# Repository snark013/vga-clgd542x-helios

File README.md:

# Helios VGA Card

[Русская версия](README_RU.md)

Main project repository: [git.snark13.com/snark13/helios](https://git.snark13.com/snark13/helios.git).

GitHub mirror: [github.com/snark013/vga-clgd542x-helios](https://github.com/snark013/vga-clgd542x-helios).

Helios is a VGA graphics card for the 16-bit ISA bus, based on Cirrus Logic CL-GD542x chips (CL-GD5422–CL-GD5429). The project is designed in KiCad and uses a two-layer PCB.

## Project status

The current schematic and PCB version is 1.2.7. The following configurations have been built and tested:

| PCB version | Graphics chip | Video memory |
| --- | --- | --- |
| 0.3 | CL-GD5422 | 512 KB |
| 1.2.5 | CL-GD5429 | 1 MB |

Other combinations of PCB revision, graphics chip, and memory capacity have not yet been tested.

Release files for version 1.2.7 are available in the repository. The test results above apply to versions 0.3 and 1.2.5.

## Key features

- VGA compatibility.
- Integrated video digital-to-analog converter (RAMDAC) with True Color support.
- Three video memory configurations: 512 KB, 1 MB, or 2 MB, depending on the graphics chip.
- Two-layer PCB for the 16-bit ISA bus.

## Video memory configurations

| Capacity | Chips to populate | Graphics chips |
| --- | --- | --- |
| 512 KB | U1 | CL-GD5422–CL-GD5424 |
| 1 MB | U1, U2 | CL-GD5422–CL-GD5429 |
| 2 MB | U1–U4 | CL-GD5426–CL-GD5429 |

This table lists the intended configurations. Configurations tested on hardware are listed under “Project status”.

## Project files

- [helios.kicad_pro](helios.kicad_pro) — KiCad project.
- [helios.kicad_sch](helios.kicad_sch) — schematic.
- [helios.kicad_pcb](helios.kicad_pcb) — PCB layout.
- [helios.pretty/](helios.pretty/) — local footprint library.
- [docs/](docs/) — reference documentation.
- [release/](release/) — release files and previous version files.
- [images/1.2.5/](images/1.2.5/) — photos of the assembled version 1.2.5 board.

### Release files

| Version | Gerber files | Schematic | Interactive bill of materials |
| --- | --- | --- | --- |
| 1.2.7 | [ZIP](release/1.2.7/helios-1.2.zip) | [PDF](release/1.2.7/helios.pdf) | [HTML](release/1.2.7/ibom.html) |
| 1.2.5 | [ZIP](release/1.2.5/helios.zip) | [PDF](release/1.2.5/helios.pdf) | [HTML](release/1.2.5/ibom.html) |

## Configuration and assembly

Component references below apply to the current revision unless stated otherwise. Check the configuration input settings against the [CL-GD542x Technical Reference Manual](docs/CL-GD542X_Technical_Reference_Manual_Jan1994.pdf) for the graphics chip being used.

### Configuration resistors

| Reference | Function |
| --- | --- |
| R9 | Zero-wait-state BIOS access (except CL-GD5429) |
| R10 | Sleep control port selection: 3C3h / 4E68h |
| R11, R12 | DRAM clock selection: 50 / 44 / 41 / 38 MHz |
| R13 | DRAM timing configuration |
| R14 | DRAM multi CAS/WE configuration |

By default, fit all resistors listed above except R10.

### Current reference

Fit only one of the two alternatives: **U5 or U5′**. These options use LM334 devices with different pinouts; select the appropriate package when assembling the board.

### Configuration jumpers

| Reference | Function |
| --- | --- |
| JP5 | Enable IRQ2 |
| JP6 | Zero-wait-state ISA operation |
| JP7 | BIOS ROM section selection |

JP6 is fitted by default.

Revisions earlier than 1.2.7 also include JP8 and JP9 to select the ROM read signal (MEMR / EROM / GND). On those boards, connect JP9 to ground. JP8 and JP9 have been removed starting with revision 1.2.7.

### Clock source

Two options are provided for the 14.318 MHz clock:

- ISA bus BOSC signal: fit R16.
- On-board oscillator: fit Y1, C17, and C18.

## BIOS preparation

A BIOS image from another graphics card may need conversion before it can be programmed into the Helios ROM.

Many original boards use a BIOS arranged for 16-bit operation with two ROM chips. The least significant address bit is used as the chip’s most significant address bit to switch between the two halves of its contents. This arrangement is described in the graphics chip documentation.

Helios uses linear (“flat”) addressing, so images with a different address arrangement must be converted. Some original boards already use linear addressing; their images do not require this conversion.

Revision **0.3** also has the BIOS data lines connected in reverse order: D0–D7 are wired as D7–D0. Images prepared for this revision must also have the bit order reversed within each byte.

## Revision history

### 1.2.7

- Corrected the mislabeled U8 device type from 74LS541 to 74LS245.
- Removed JP8 and JP9.
- Removed unnecessary PCB markings and corrected inaccurate ones.

### 1.2.5

- Optimized component placement.
- Changed all capacitors below 0.1 µF to the 0603 package.
- Added diode protection to the VGA output lines.
- Built the second working board version.

### 1.2.2

- Optimized component placement.
- Renumbered components.

### 0.7

- Added an alternative HC-49 footprint for the 14.318 MHz oscillator.

### 0.5

- Added support for an on-board 14.318 MHz oscillator (two-pin 5032 package).
- Added support for the LM334SM with an alternative pinout as a current reference.
- Corrected the BIOS data bus routing.
- Added termination resistors to the address bus lines between the graphics chip and memory.
- Renumbered components.

### 0.3

- Built the first working board, codenamed Lemon.
- Identified the reversed BIOS data line order (D0–D7 → D7–D0); the BIOS image requires a corresponding conversion.

## Photos

Assembled version 1.2.5 board.

[Photo of the revision 0.3 board](images/0.3/build-0.3.jpg).

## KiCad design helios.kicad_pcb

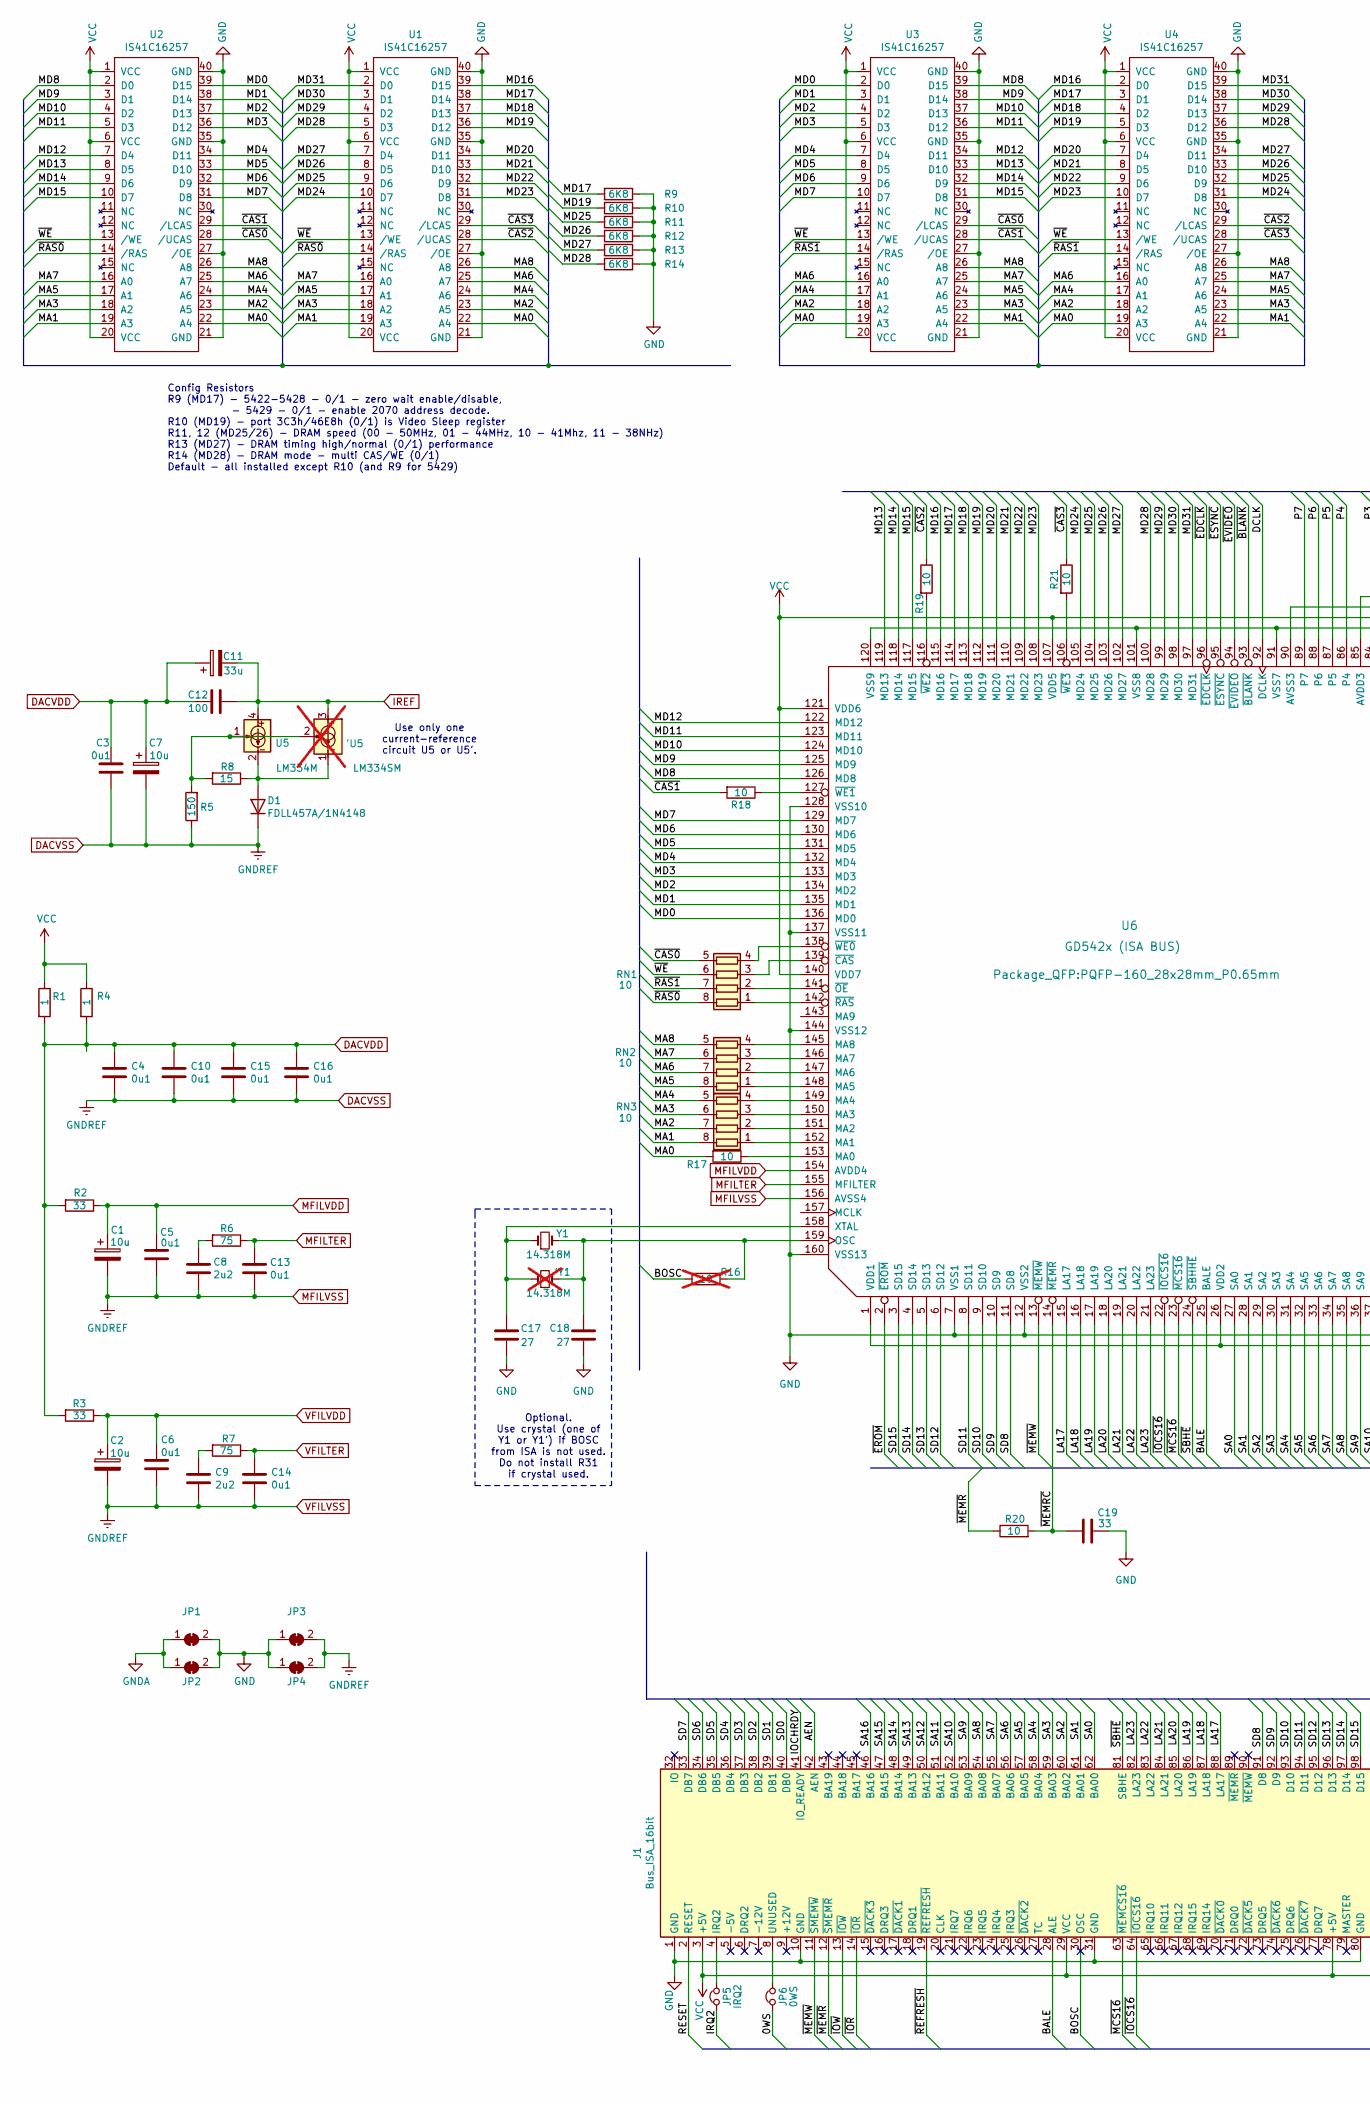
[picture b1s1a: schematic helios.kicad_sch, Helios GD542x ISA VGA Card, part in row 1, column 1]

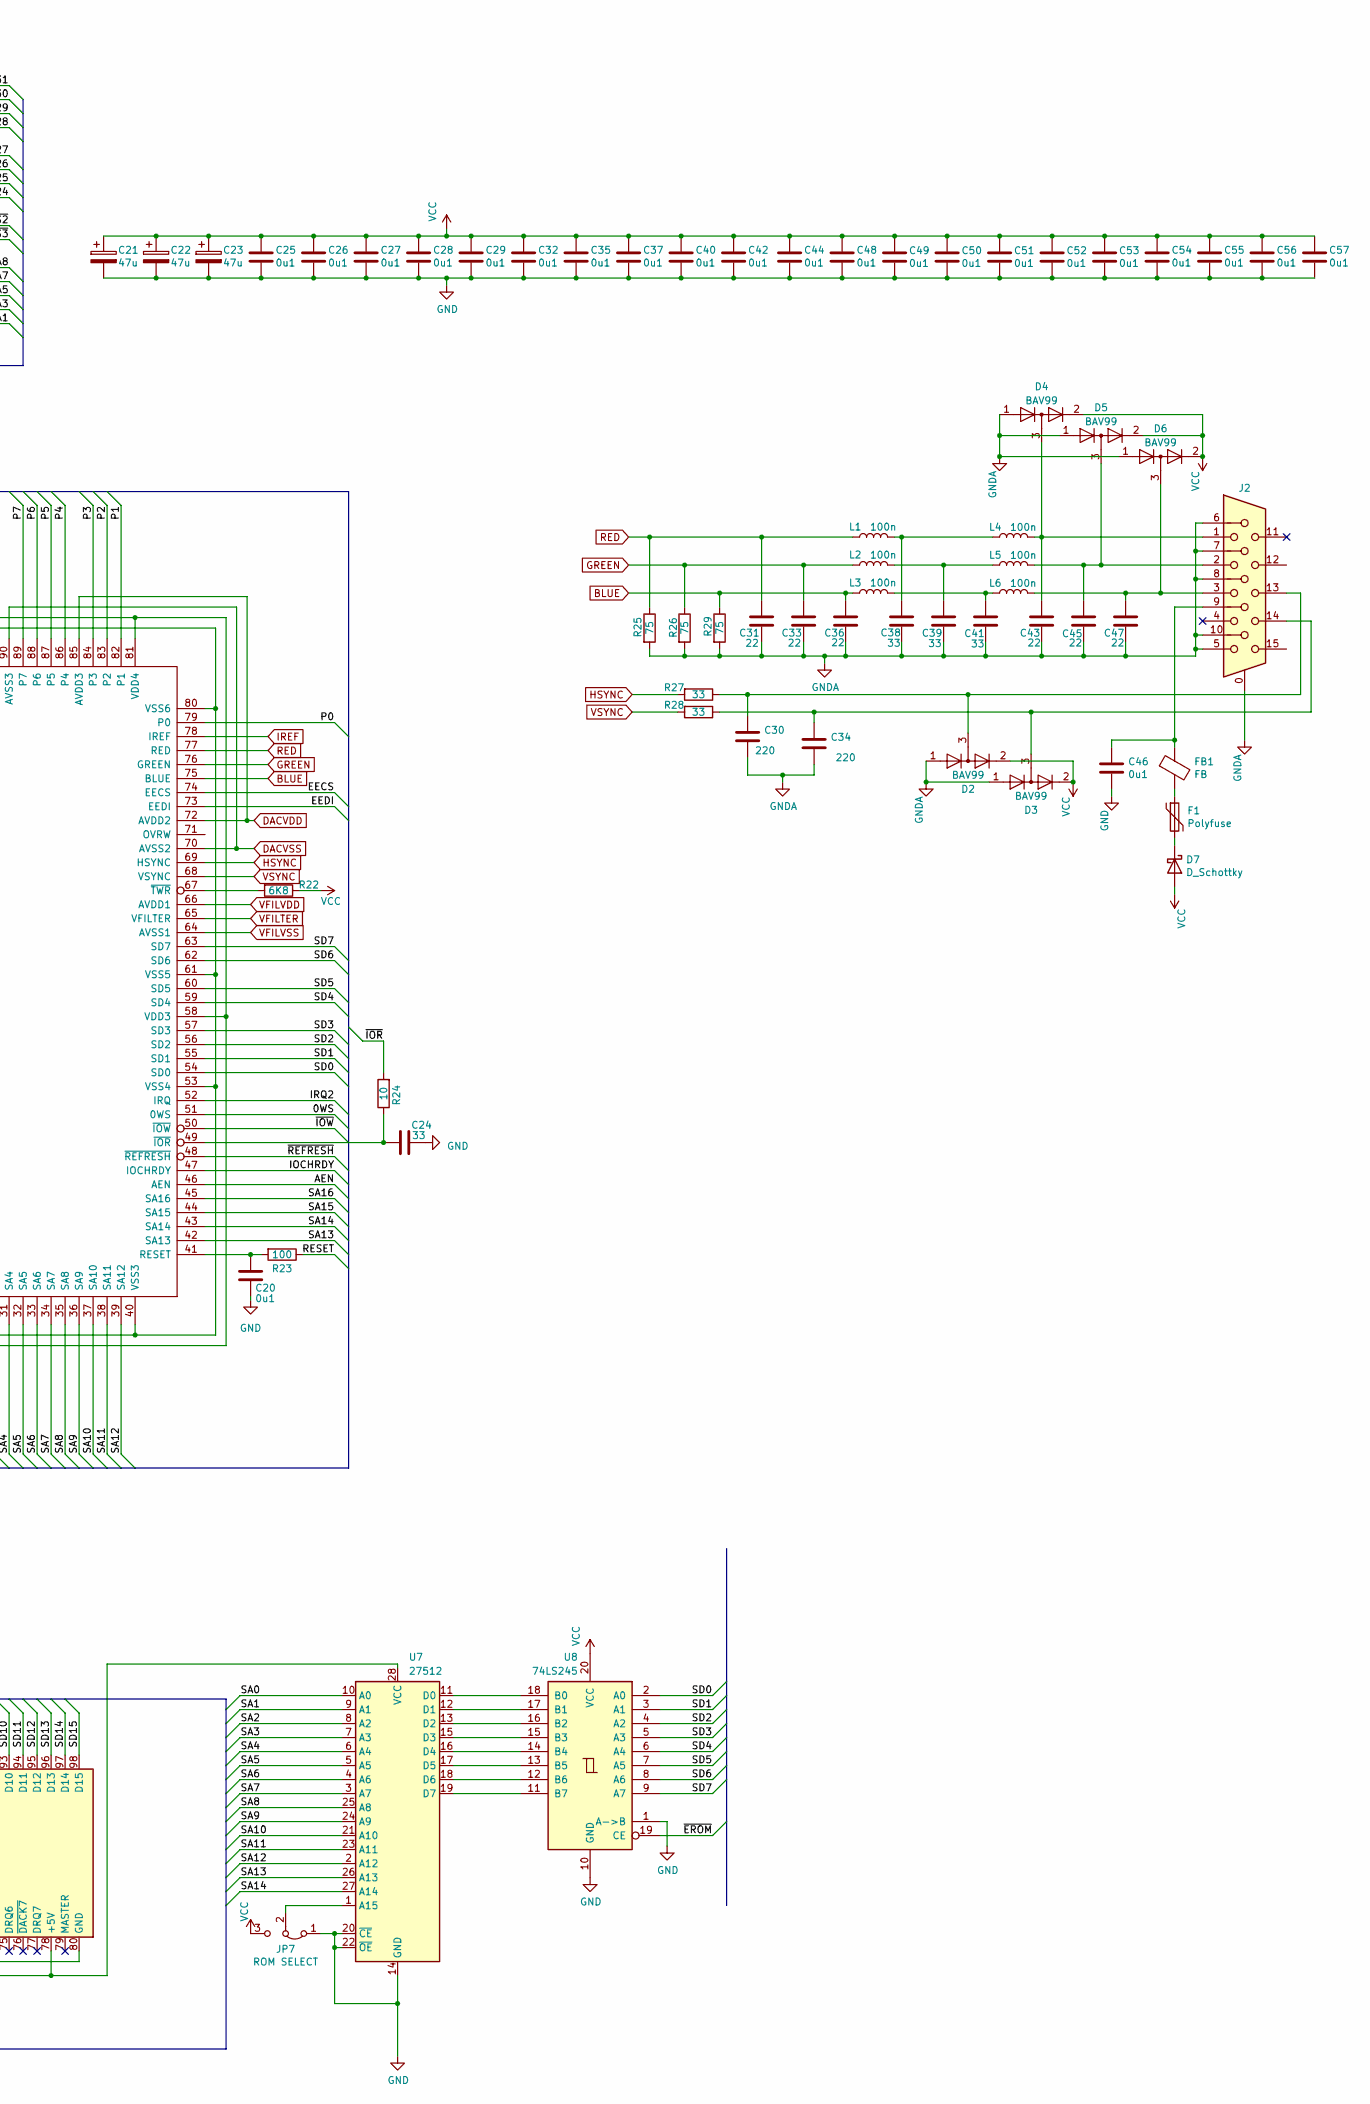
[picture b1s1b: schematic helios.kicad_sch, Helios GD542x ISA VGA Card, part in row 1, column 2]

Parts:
'U5: LM334SM; SOIC-8_3.9x4.9mm_P1.27mm; not fitted
'Y1: 14.318M; Crystal_HC49-U_Vertical; not fitted
C1, C2: 10u; CP_EIA-3216-18_Kemet-A_Pad1.58x1.35mm_HandSolder
C3, C4, C5, C6, C13, C14, C15, C16, C25, C26, C27, C28, C29, C32, C35, C37, C40, C42, C44, C46, C48, C49, C50, C51, C52, C53, C54, C55, C56, C57: 0u1; C_0805_2012Metric_Pad1.18x1.45mm_HandSolder
C7: 10u; CP_EIA-3216-18_Kemet-A
C8, C9: 2u2; C_0805_2012Metric
C10: 0u1; C_0805_2012Metric
C11: 33u; CP_EIA-3216-18_Kemet-A
C12: 100; C_0603_1608Metric_Pad1.08x0.95mm_HandSolder
C17, C18: 27; C_0603_1608Metric_Pad1.08x0.95mm_HandSolder
C19, C24, C38, C39, C41: 33; C_0603_1608Metric_Pad1.08x0.95mm_HandSolder
C20: 0u1; C_0603_1608Metric_Pad1.08x0.95mm_HandSolder
C21, C22, C23: 47u; CP_EIA-3216-18_Kemet-A
C30, C34: 220; C_0603_1608Metric_Pad1.08x0.95mm_HandSolder
C31, C33, C36, C43, C45, C47: 22; C_0603_1608Metric_Pad1.08x0.95mm_HandSolder
D1: FDLL457A/1N4148; D_MiniMELF_Handsoldering
D2, D3, D4, D5, D6: BAV99; SOT-23
D7: D_Schottky; D_MELF-RM10_Universal_Handsoldering
F1: Polyfuse; Fuse_0805_2012Metric_Pad1.15x1.40mm_HandSolder
FB1: FB; L_0805_2012Metric_Pad1.15x1.40mm_HandSolder
J1: Bus_ISA_16bit; BUS_AT
J2: DB15_Female_HighDensity_MountingHoles; DSUB-15-HD_Female_Horizontal_P2.29x1.98mm_EdgePinOffset3.03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
JP1, JP2, JP3, JP4: SolderJumper_2_Bridged; NonSolderJumper-2_P1.3mm_Bridged2Bar_Pad1.0x1.5mm
JP5: IRQ2; PinHeader_1x02_P2.54mm_Vertical
JP6: 0WS; PinHeader_1x02_P2.54mm_Vertical
JP7: ROM SELECT; PinHeader_1x03_P2.54mm_Vertical
L1, L2, L3, L4, L5, L6: 100n; L_0805_2012Metric_Pad1.15x1.40mm_HandSolder
R1, R4: 1; R_0603_1608Metric
R2, R3, R27, R28: 33; R_0603_1608Metric
R5: 150; R_0603_1608Metric
R6, R7, R25, R26, R29: 75; R_0603_1608Metric
R8: 15; R_0603_1608Metric
R9, R10, R11, R12, R13, R14, R22: 6K8; R_0603_1608Metric
R16: 10; R_0603_1608Metric; not fitted
R17, R18, R19, R21: 10; R_0402_1005Metric_Pad0.72x0.64mm_HandSolder
R20, R24: 10; R_0603_1608Metric
R23: 100; R_0603_1608Metric
RN1, RN2, RN3: 10; R_Array_Concave_4x0603
U1, U2, U3, U4: IS41C16257; SOJ-40-Socket-LongPads
U5: LM334M; SOIC-8_3.9x4.9mm_P1.27mm
U6: GD542x (ISA BUS); PQFP-160_28x28mm_P0.65mm
U7: 27512; DIP-28_W15.24mm
U8: 74LS245; DIP-20_W7.62mm
Y1: 14.318M; Crystal_SMD_5032-2Pin_5.0x3.2mm_HandSoldering

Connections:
/0WS: JP6.1, U6.51 (0WS)
/AEN: J1.42 (AEN), U6.46 (AEN)
/BALE: J1.28 (ALE), U6.25 (BALE)
/BOSC: J1.30 (OSC), R16.2
/DCLK: U6.92 (DCLK)
/EECS: U6.74 (EECS)
/EEDI: U6.73 (EEDI)
/IOCHRDY: J1.41 (IO_READY), U6.47 (IOCHRDY)
/IRQ2: JP5.1, U6.52 (IRQ)
/LA17: J1.88 (LA17), U6.15 (LA17)
/LA18: J1.87 (LA18), U6.16 (LA18)
/LA19: J1.86 (LA19), U6.17 (LA19)
/LA20: J1.85 (LA20), U6.18 (LA20)
/LA21: J1.84 (LA21), U6.19 (LA21)
/LA22: J1.83 (LA22), U6.20 (LA22)
/LA23: J1.82 (LA23), U6.21 (LA23)
/MA0: R17.2, U1.22 (A4), U2.22 (A4), U3.19 (A3), U4.19 (A3)
/MA1: RN3.8 (R1.2), U1.19 (A3), U2.19 (A3), U3.22 (A4), U4.22 (A4)
/MA2: RN3.7 (R2.2), U1.23 (A5), U2.23 (A5), U3.18 (A2), U4.18 (A2)
/MA3: RN3.6 (R3.2), U1.18 (A2), U2.18 (A2), U3.23 (A5), U4.23 (A5)
/MA4: RN3.5 (R4.2), U1.24 (A6), U2.24 (A6), U3.17 (A1), U4.17 (A1)
/MA5: RN2.8 (R1.2), U1.17 (A1), U2.17 (A1), U3.24 (A6), U4.24 (A6)
/MA6: RN2.7 (R2.2), U1.25 (A7), U2.25 (A7), U3.16 (A0), U4.16 (A0)
/MA7: RN2.6 (R3.2), U1.16 (A0), U2.16 (A0), U3.25 (A7), U4.25 (A7)
/MA8: RN2.5 (R4.2), U1.26 (A8), U2.26 (A8), U3.26 (A8), U4.26 (A8)
/MD0: U2.39 (D15), U3.2 (D0), U6.136 (MD0)
/MD1: U2.38 (D14), U3.3 (D1), U6.135 (MD1)
/MD2: U2.37 (D13), U3.4 (D2), U6.134 (MD2)
/MD3: U2.36 (D12), U3.5 (D3), U6.133 (MD3)
/MD4: U2.34 (D11), U3.7 (D4), U6.132 (MD4)
/MD5: U2.33 (D10), U3.8 (D5), U6.131 (MD5)
/MD6: U2.32 (D9), U3.9 (D6), U6.130 (MD6)
/MD7: U2.31 (D8), U3.10 (D7), U6.129 (MD7)
/MD8: U2.2 (D0), U3.39 (D15), U6.126 (MD8)
/MD9: U2.3 (D1), U3.38 (D14), U6.125 (MD9)
/MD10: U2.4 (D2), U3.37 (D13), U6.124 (MD10)
/MD11: U2.5 (D3), U3.36 (D12), U6.123 (MD11)
/MD12: U2.7 (D4), U3.34 (D11), U6.122 (MD12)
/MD13: U2.8 (D5), U3.33 (D10), U6.119 (MD13)
/MD14: U2.9 (D6), U3.32 (D9), U6.118 (MD14)
/MD15: U2.10 (D7), U3.31 (D8), U6.117 (MD15)
/MD16: U1.39 (D15), U4.2 (D0), U6.115 (MD16)
/MD17: R9.2, U1.38 (D14), U4.3 (D1), U6.114 (MD17)
/MD18: U1.37 (D13), U4.4 (D2), U6.113 (MD18)
/MD19: R10.2, U1.36 (D12), U4.5 (D3), U6.112 (MD19)
/MD20: U1.34 (D11), U4.7 (D4), U6.111 (MD20)
/MD21: U1.33 (D10), U4.8 (D5), U6.110 (MD21)
/MD22: U1.32 (D9), U4.9 (D6), U6.109 (MD22)
/MD23: U1.31 (D8), U4.10 (D7), U6.108 (MD23)
/MD24: U1.10 (D7), U4.31 (D8), U6.105 (MD24)
/MD25: R11.2, U1.9 (D6), U4.32 (D9), U6.104 (MD25)
/MD26: R12.2, U1.8 (D5), U4.33 (D10), U6.103 (MD26)
/MD27: R13.2, U1.7 (D4), U4.34 (D11), U6.102 (MD27)
/MD28: R14.2, U1.5 (D3), U4.36 (D12), U6.100 (MD28)
/MD29: U1.4 (D2), U4.37 (D13), U6.99 (MD29)
/MD30: U1.3 (D1), U4.38 (D14), U6.98 (MD30)
/MD31: U1.2 (D0), U4.39 (D15), U6.97 (MD31)
/P0: U6.79 (P0)
/P1: U6.82 (P1)
/P2: U6.83 (P2)
/P3: U6.84 (P3)
/P4: U6.86 (P4)
/P5: U6.87 (P5)
/P6: U6.88 (P6)
/P7: U6.89 (P7)
/RESET: J1.2 (RESET), R23.1
/SA0: J1.62 (BA00), U6.27 (SA0), U7.10 (A0)
/SA1: J1.61 (BA01), U6.28 (SA1), U7.9 (A1)
/SA2: J1.60 (BA02), U6.29 (SA2), U7.8 (A2)
/SA3: J1.59 (BA03), U6.30 (SA3), U7.7 (A3)
/SA4: J1.58 (BA04), U6.31 (SA4), U7.6 (A4)
/SA5: J1.57 (BA05), U6.32 (SA5), U7.5 (A5)
/SA6: J1.56 (BA06), U6.33 (SA6), U7.4 (A6)
/SA7: J1.55 (BA07), U6.34 (SA7), U7.3 (A7)
/SA8: J1.54 (BA08), U6.35 (SA8), U7.25 (A8)
/SA9: J1.53 (BA09), U6.36 (SA9), U7.24 (A9)
/SA10: J1.52 (BA10), U6.37 (SA10), U7.21 (A10)
/SA11: J1.51 (BA11), U6.38 (SA11), U7.23 (A11)
/SA12: J1.50 (BA12), U6.39 (SA12), U7.2 (A12)
/SA13: J1.49 (BA13), U6.42 (SA13), U7.26 (A13)
/SA14: J1.48 (BA14), U6.43 (SA14), U7.27 (A14)
/SA15: J1.47 (BA15), U6.44 (SA15)
/SA16: J1.46 (BA16), U6.45 (SA16)
/SD0: J1.40 (DB0), U6.54 (SD0), U8.2 (A0)
/SD1: J1.39 (DB1), U6.55 (SD1), U8.3 (A1)
/SD2: J1.38 (DB2), U6.56 (SD2), U8.4 (A2)
/SD3: J1.37 (DB3), U6.57 (SD3), U8.5 (A3)
/SD4: J1.36 (DB4), U6.59 (SD4), U8.6 (A4)
/SD5: J1.35 (DB5), U6.60 (SD5), U8.7 (A5)
/SD6: J1.34 (DB6), U6.62 (SD6), U8.8 (A6)
/SD7: J1.33 (DB7), U6.63 (SD7), U8.9 (A7)
/SD8: J1.91 (D8), U6.11 (SD8)
/SD9: J1.92 (D9), U6.10 (SD9)
/SD10: J1.93 (D10), U6.9 (SD10)
/SD11: J1.94 (D11), U6.8 (SD11)
/SD12: J1.95 (D12), U6.6 (SD12)
/SD13: J1.96 (D13), U6.5 (SD13)
/SD14: J1.97 (D14), U6.4 (SD14)
/SD15: J1.98 (D15), U6.3 (SD15)
/~BLANK: U6.93 (~BLANK)
/~CAS0: RN1.5 (R4.2), U2.28 (/UCAS), U3.29 (/LCAS)
/~CAS1: R18.2, U2.29 (/LCAS), U3.28 (/UCAS)
/~CAS2: R19.1, U1.28 (/UCAS), U4.29 (/LCAS)
/~CAS3: R21.1, U1.29 (/LCAS), U4.28 (/UCAS)
/~EDCLK: U6.96 (~EDCLK)
/~EROM: U6.2 (~EROM), U8.19 (CE)
/~ESYNC: U6.95 (~ESYNC)
/~EVIDEO: U6.94 (~EVIDEO)
/~IOCS16: J1.64 (~IOCS16), U6.22 (~IOCS16)
/~IOR: J1.14 (~IOR), R24.2
/~IOW: J1.13 (~IOW), U6.50 (~IOW)
/~MCS16: J1.63 (~MEMCS16), U6.23 (~MCS16)
/~MEMRC: C19.2, R20.2, U6.14 (~MEMR)
/~MEMR: J1.12 (~SMEMR), R20.1
/~MEMW: J1.11 (~SMEMW), U6.13 (~MEMW)
/~RAS0: RN1.8 (R1.2), U1.14 (/RAS), U2.14 (/RAS)
/~RAS1: RN1.7 (R2.2), U3.14 (/RAS), U4.14 (/RAS)
/~REFRESH: J1.19 (~REFRESH), U6.48 (~REFRESH)
/~SBHE: J1.81 (SBHE), U6.24 (~SBHHE)
/~WE: RN1.6 (R3.2), U1.13 (/WE), U2.13 (/WE), U3.13 (/WE), U4.13 (/WE)
BLUE: C36.1, L3.1, R29.1, U6.75 (BLUE)
DACVDD: C3.1, C4.1, C7.1, C10.1, C11.1, C12.1, C15.1, C16.1, R1.2, R2.2, R3.2, R4.2, U6.72 (AVDD2), U6.85 (AVDD3)
DACVSS: C1.2, C2.2, C3.2, C4.2, C5.2, C6.2, C7.2, C8.2, C9.2, C10.2, C13.2, C14.2, C15.2, C16.2, D1.1 (K), JP3.2 (B), JP4.2 (B), R5.1, U6.64 (AVSS1), U6.70 (AVSS2), U6.90 (AVSS3), U6.156 (AVSS4)
GND: C17.2, C18.2, C19.1, C20.2, C21.2, C22.2, C23.2, C24.1, C25.2, C26.2, C27.2, C28.2, C29.2, C32.2, C35.2, C37.2, C40.2, C42.2, C44.2, C46.2, C48.2, C49.2, C50.2, C51.2, C52.2, C53.2, C54.2, C55.2, C56.2, C57.2, J1.1 (GND), J1.10 (GND), J1.31 (GND), J1.80 (GND), JP1.2 (B), JP2.2 (B), JP3.1 (A), JP4.1 (A), JP7.1 (A), R9.1, R10.1, R11.1, R12.1, R13.1, R14.1, U1.21 (GND), U1.27 (/OE), U1.35 (GND), U1.40 (GND), U2.21 (GND), U2.27 (/OE), U2.35 (GND), U2.40 (GND), U3.21 (GND), U3.27 (/OE), U3.35 (GND), U3.40 (GND), U4.21 (GND), U4.27 (/OE), U4.35 (GND), U4.40 (GND), U6.7 (VSS1), U6.12 (VSS2), U6.40 (VSS3), U6.53 (VSS4), U6.61 (VSS5), U6.80 (VSS6), U6.91 (VSS7), U6.101 (VSS8), U6.120 (VSS9), U6.128 (VSS10), U6.137 (VSS11), U6.144 (VSS12), U6.160 (VSS13), U7.14 (GND), U7.20 (~CE), U7.22 (~OE), U8.1 (A->B), U8.10 (GND)
GNDA: C30.2, C31.2, C33.2, C34.2, C36.2, C38.2, C39.2, C41.2, C43.2, C45.2, C47.2, D2.1 (K), D3.1 (K), D4.1 (K), D5.1 (K), D6.1 (K), J2.0, J2.5, J2.6, J2.7, J2.8, J2.10, JP1.1 (A), JP2.1 (A), R25.2, R26.2, R29.2
GREEN: C33.1, L2.1, R26.1, U6.76 (GREEN)
HSYNC: R27.2, U6.69 (HSYNC)
IREF: 'U5.3, C11.2, C12.2, U5.4, U6.78 (IREF)
MFILTER: C13.1, R6.1, U6.155 (MFILTER)
MFILVDD: C1.1, C5.1, R2.1, U6.154 (AVDD4)
unnamed: 'U5.2, R5.2, R8.2, U5.1
unnamed: C8.1, R6.2
unnamed: C9.1, R7.2
unnamed: C30.1, D2.3 (K), J2.13, R27.1
unnamed: C34.1, D3.3 (K), J2.14, R28.1
unnamed: C38.1, L1.2, L4.1
unnamed: C39.1, L2.2, L5.1
unnamed: C41.1, L3.2, L6.1
unnamed: C43.1, D4.3 (K), J2.1, L4.2
unnamed: C45.1, D5.3 (K), J2.2, L5.2
unnamed: C46.1, FB1.1, J2.9
unnamed: C47.1, D6.3 (K), J2.3, L6.2
unnamed: 'U5.1, D1.2 (A), R8.1, U5.2, U5.3, U5.6, U5.7
unnamed: D7.1 (K), F1.2
unnamed: F1.1, FB1.2
unnamed: J1.4 (IRQ2), JP5.2
unnamed: J1.8 (UNUSED), JP6.2
unnamed: JP7.2 (C), U7.1 (A15)
unnamed: RN1.1 (R1.1), U6.142 (~RAS)
unnamed: RN1.2 (R2.1), U6.141 (~OE)
unnamed: RN1.3 (R3.1), U6.139 (~CAS)
unnamed: RN1.4 (R4.1), U6.138 (~WE0)
unnamed: RN2.1 (R1.1), U6.148 (MA5)
unnamed: RN2.2 (R2.1), U6.147 (MA6)
unnamed: RN2.3 (R3.1), U6.146 (MA7)
unnamed: RN2.4 (R4.1), U6.145 (MA8)
unnamed: RN3.1 (R1.1), U6.152 (MA1)
unnamed: RN3.2 (R2.1), U6.151 (MA2)
unnamed: RN3.3 (R3.1), U6.150 (MA3)
unnamed: RN3.4 (R4.1), U6.149 (MA4)
unnamed: R17.1, U6.153 (MA0)
unnamed: 'Y1.2, C18.1, R16.1, U6.159 (OSC), Y1.2
unnamed: C20.1, R23.2, U6.41 (RESET)
unnamed: 'Y1.1, C17.1, U6.158 (XTAL), Y1.1
unnamed: C24.2, R24.1, U6.49 (~IOR)
unnamed: R22.2, U6.67 (~TWR)
unnamed: R18.1, U6.127 (~WE1)
unnamed: R19.2, U6.116 (~WE2)
unnamed: R21.2, U6.106 (~WE3)
unnamed: U7.11 (D0), U8.18 (B0)
unnamed: U7.12 (D1), U8.17 (B1)
unnamed: U7.13 (D2), U8.16 (B2)
unnamed: U7.15 (D3), U8.15 (B3)
unnamed: U7.16 (D4), U8.14 (B4)
unnamed: U7.17 (D5), U8.13 (B5)
unnamed: U7.18 (D6), U8.12 (B6)
unnamed: U7.19 (D7), U8.11 (B7)
RED: C31.1, L1.1, R25.1, U6.77 (RED)
VCC: C21.1, C22.1, C23.1, C25.1, C26.1, C27.1, C28.1, C29.1, C32.1, C35.1, C37.1, C40.1, C42.1, C44.1, C48.1, C49.1, C50.1, C51.1, C52.1, C53.1, C54.1, C55.1, C56.1, C57.1, D2.2 (A), D3.2 (A), D4.2 (A), D5.2 (A), D6.2 (A), D7.2 (A), J1.3 (+5V), J1.29 (VCC), J1.78 (+5V), JP7.3 (B), R1.1, R4.1, R22.1, U1.1 (VCC), U1.6 (VCC), U1.20 (VCC), U2.1 (VCC), U2.6 (VCC), U2.20 (VCC), U3.1 (VCC), U3.6 (VCC), U3.20 (VCC), U4.1 (VCC), U4.6 (VCC), U4.20 (VCC), U6.1 (VDD1), U6.26 (VDD2), U6.58 (VDD3), U6.81 (VDD4), U6.107 (VDD5), U6.121 (VDD6), U6.140 (VDD7), U7.28 (VCC), U8.20 (VCC)
VFILTER: C14.1, R7.1, U6.65 (VFILTER)
VFILVDD: C2.1, C6.1, R3.1, U6.66 (AVDD1)
VSYNC: R28.2, U6.68 (VSYNC)

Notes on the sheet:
Config Resistors R9 (MD17) - 5422-5428 - 0/1 - zero wait enable/disable, - 5429 - 0/1 - enable 2070 address decode. R10 (MD19) - port 3C3h/46E8h (0/1) is Video Sleep register R11, 12 (MD25/26) - DRAM speed (00 - 50MHz, 01 - 44MHz, 10 - 41Mhz, 11 - 38NHz) R13 (MD27) - DRAM timing high/normal (0/1) p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
Optional. Use crystal (one of Y1 or Y1') if BOSC from ISA is not used. Do not install R31 if crystal used.
Use only one current-reference circuit U5 or U5'.

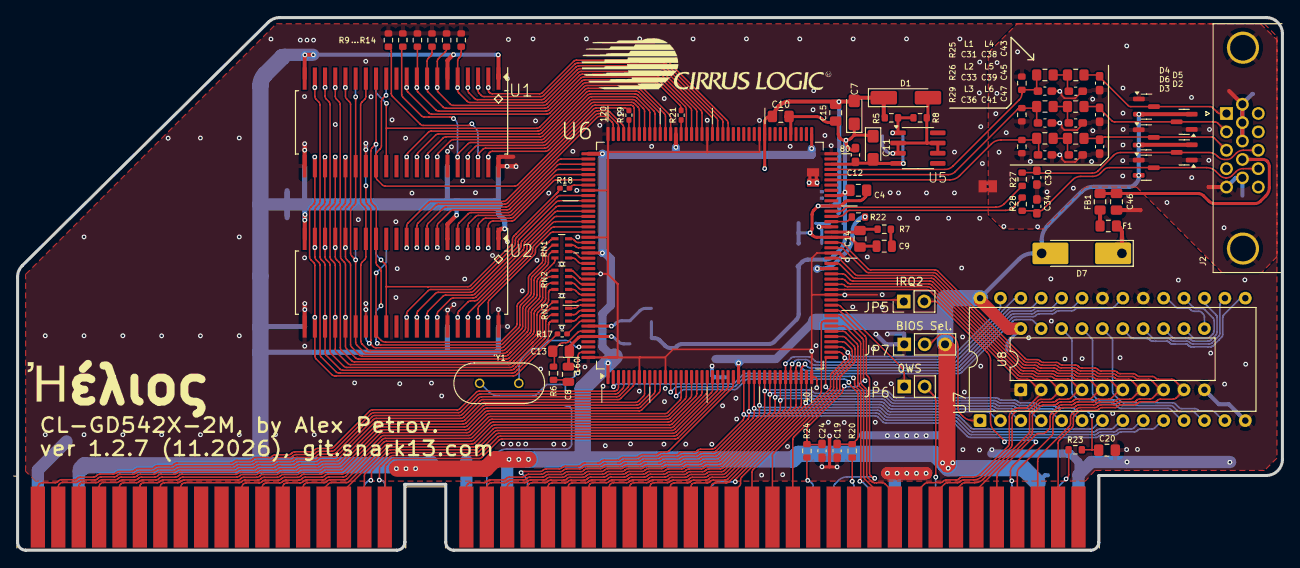
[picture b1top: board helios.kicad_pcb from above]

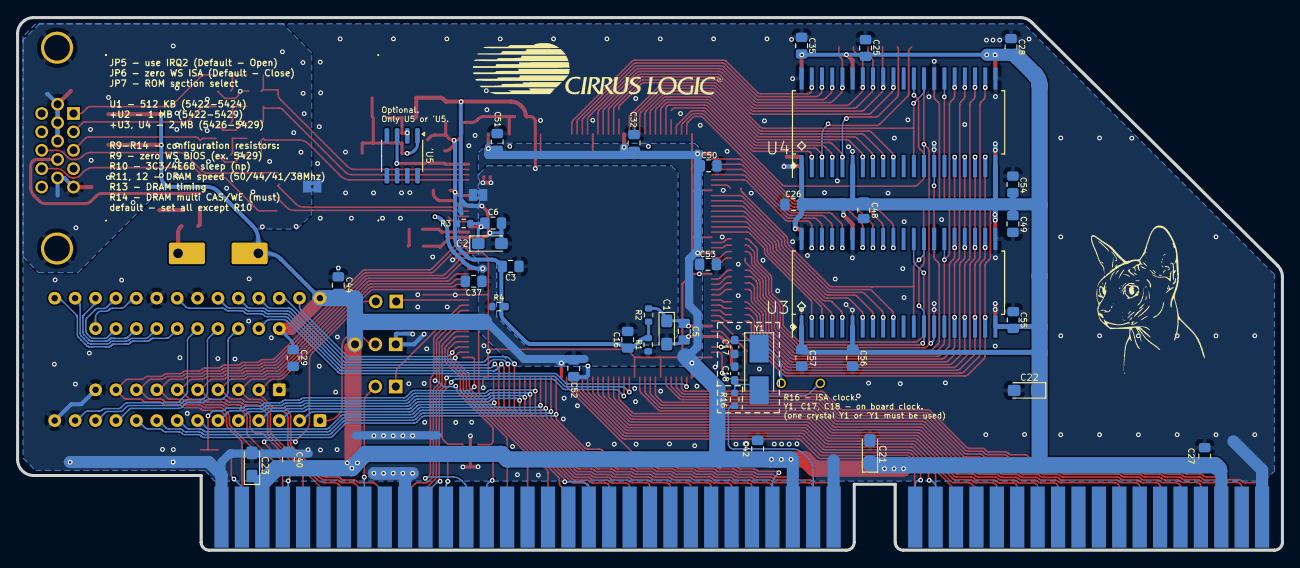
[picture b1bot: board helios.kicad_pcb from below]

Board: 2 copper layers, 157.4 x 66.3 mm, 123 parts (43 on the bottom side), 167 nets.
